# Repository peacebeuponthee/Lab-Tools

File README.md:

# Lab-Tools

1. Oscilloscope differential probe
2. Ultralow distortion sinewave generator

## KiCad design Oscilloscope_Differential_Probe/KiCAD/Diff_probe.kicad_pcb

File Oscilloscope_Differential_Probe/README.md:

Oscilloscope differential probe project based on reference design of Analog Devices.

The probe is based on the LTC6268-10 - 4GHz Ultra-Low Bias Current FET Input Op Amp from Analog Devices
https://www.analog.com/en/products/ltc6268-10.html#product-overview

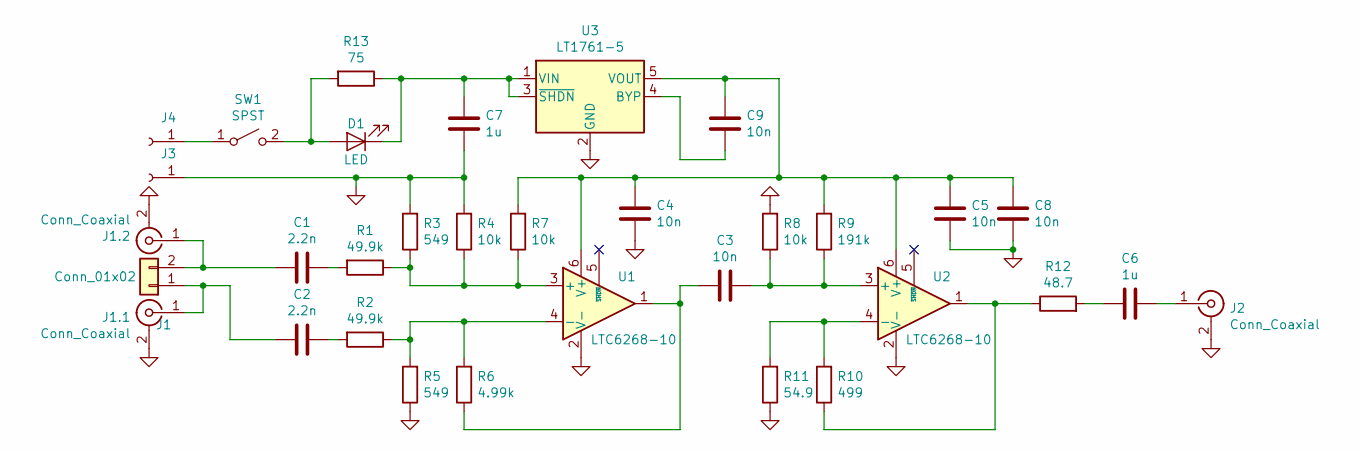
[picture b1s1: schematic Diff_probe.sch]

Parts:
C1, C2: 2.2n; C_1210_3225Metric; MouserID 80-C1210C222JDGAUTO
C3, C4, C5, C8, C9: 10n; C_0805_2012Metric; MouserID 80-C0805C103J5GECLR
C6, C7: 1u; C_0805_2012Metric; MouserID 80-C0805C105K4R
D1: LED; LED_1206_3216Metric; MouserID 604-APT3216LSECKJ4RV
J1: Conn_01x02; PinHeader_1x02_P2.54mm_Vertical; MouserID TSW-104-12-T-S-RA
J1.1, J1.2, J2: Conn_Coaxial; SMA_Samtec_SMA-J-P-X-ST-EM1_EdgeMount; MouserID 223-CON-SMA-EDGE-S
J3: Conn_01x01_Female; BatteryHolder_Keystone_593; MouserID 534-593
J4: Conn_01x01_Female; BatteryHolder_Keystone_594; MouserID 534-594
R1, R2: 49.9k; R_0805_2012Metric; MouserID 284-APC0805B49K9N
R3, R5: 549; R_0805_2012Metric; MouserID 667-ERA-6AEB5490V
R4, R7, R8: 10k; R_0805_2012Metric; MouserID 284-APC0805B10K0N
R6: 4.99k; R_0805_2012Metric; MouserID 284-APC0805B4K99N
R9: 191k; R_0805_2012Metric; MouserID 667-ERA-6AEB1913V
R10: 499; R_0805_2012Metric; MouserID 284-APC0805B499RN
R11: 54.9; R_0805_2012Metric; MouserID 667-ERA-6AEB54R9V
R12: 48.7; R_0805_2012Metric; MouserID 667-ERA-6AEB48R7V
R13: 75; R_1206_3216Metric; MouserID 71-CRCW120675R0FKEAC
SW1: SPST; SW_DIP_SPSTx01_Slide_6.7x4.1mm_W8.61mm_P2.54mm_LowProfile; MouserID 642-DM01
U1, U2: LTC6268-10; SOT-23-6; MouserID 584-C6268IS6-10TMPF
U3: LT1761-5; TSOT-23-5; MouserID 584-LT1761ES5-5TRPBF

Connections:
GND: C4.1, C5.1, C7.1, C8.1, J1.1.2 (Ext), J1.2.2 (Ext), J2.2 (Ext), J3.1, R3.2, R4.2, R5.1, R8.2, R11.1, U1.2 (V-), U2.2 (V-), U3.2 (GND)
unnamed: C1.1, R1.2
unnamed: C1.2, J1.2, J1.2.1 (In)
unnamed: C2.1, R2.2
unnamed: C2.2, J1.1, J1.1.1 (In)
unnamed: C3.1, R8.1, R9.1, U2.3 (+)
unnamed: C3.2, R6.1, U1.1
unnamed: C4.2, C5.2, C8.2, C9.2, R7.2, R9.2, U1.6 (V+), U2.6 (V+), U3.5 (VOUT)
unnamed: C6.1, R12.2
unnamed: C6.2, J2.1 (In)
unnamed: C7.2, D1.1 (K), R13.1, U3.1 (VIN), U3.3 (~SHDN)
unnamed: C9.1, U3.4 (BYP)
unnamed: D1.2 (A), R13.2, SW1.2 (B)
unnamed: J4.1, SW1.1 (A)
unnamed: R1.1, R3.1, R4.1, R7.1, U1.3 (+)
unnamed: R2.1, R5.2, R6.2, U1.4 (-)
unnamed: R10.1, R12.1, U2.1
unnamed: R10.2, R11.2, U2.4 (-)

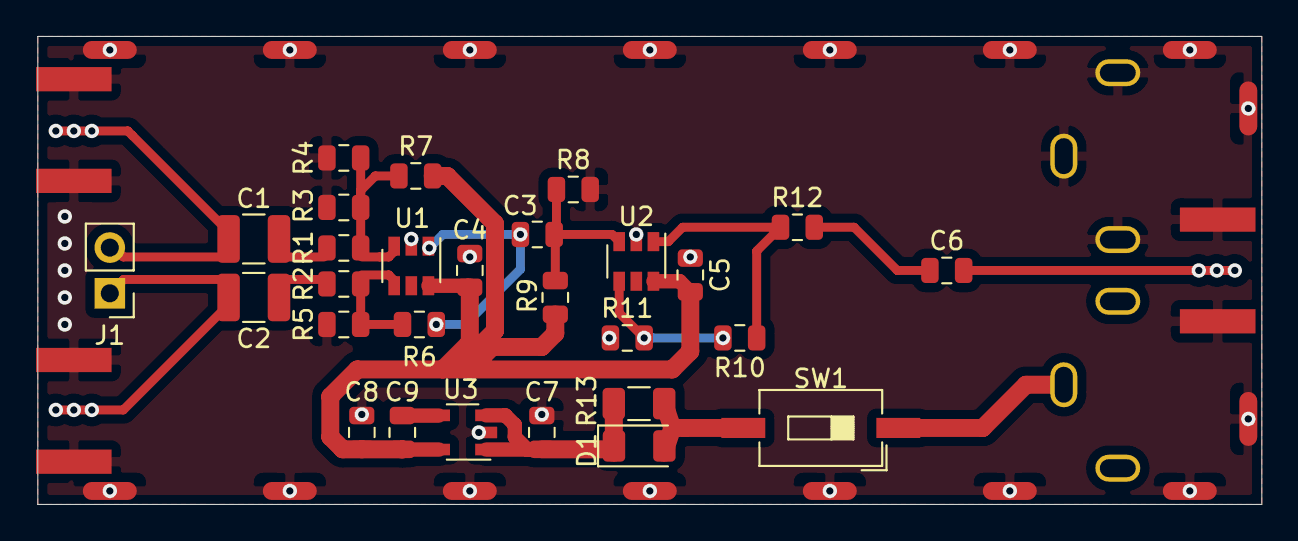
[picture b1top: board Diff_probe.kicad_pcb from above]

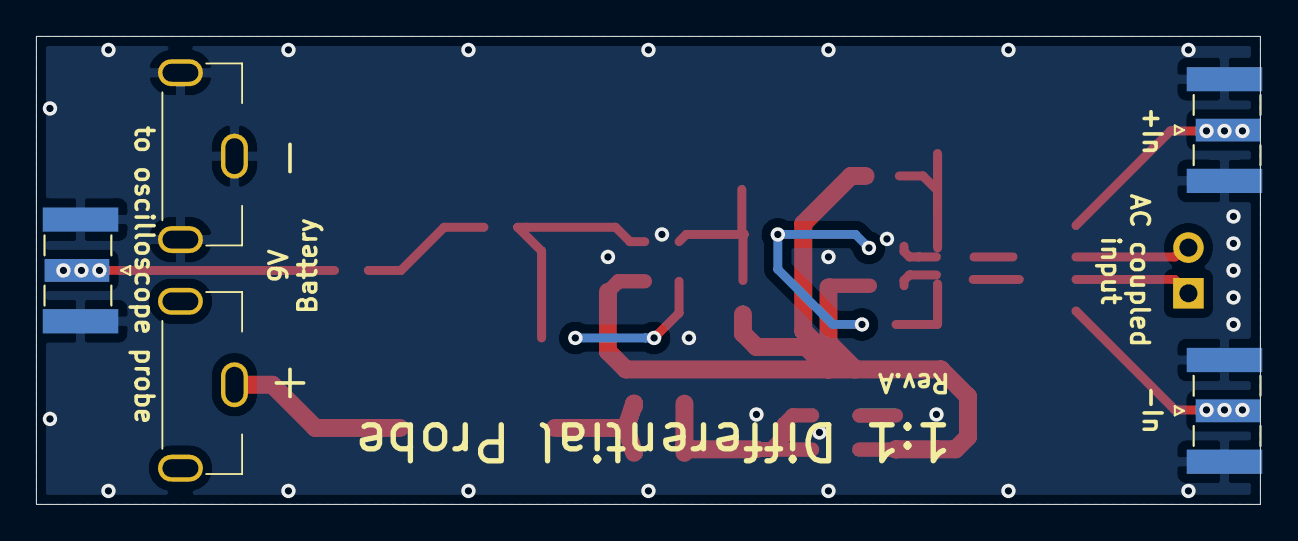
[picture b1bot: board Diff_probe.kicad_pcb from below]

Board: 2 copper layers, 68.0 x 26.0 mm, 33 parts (5 on the bottom side), 18 nets.

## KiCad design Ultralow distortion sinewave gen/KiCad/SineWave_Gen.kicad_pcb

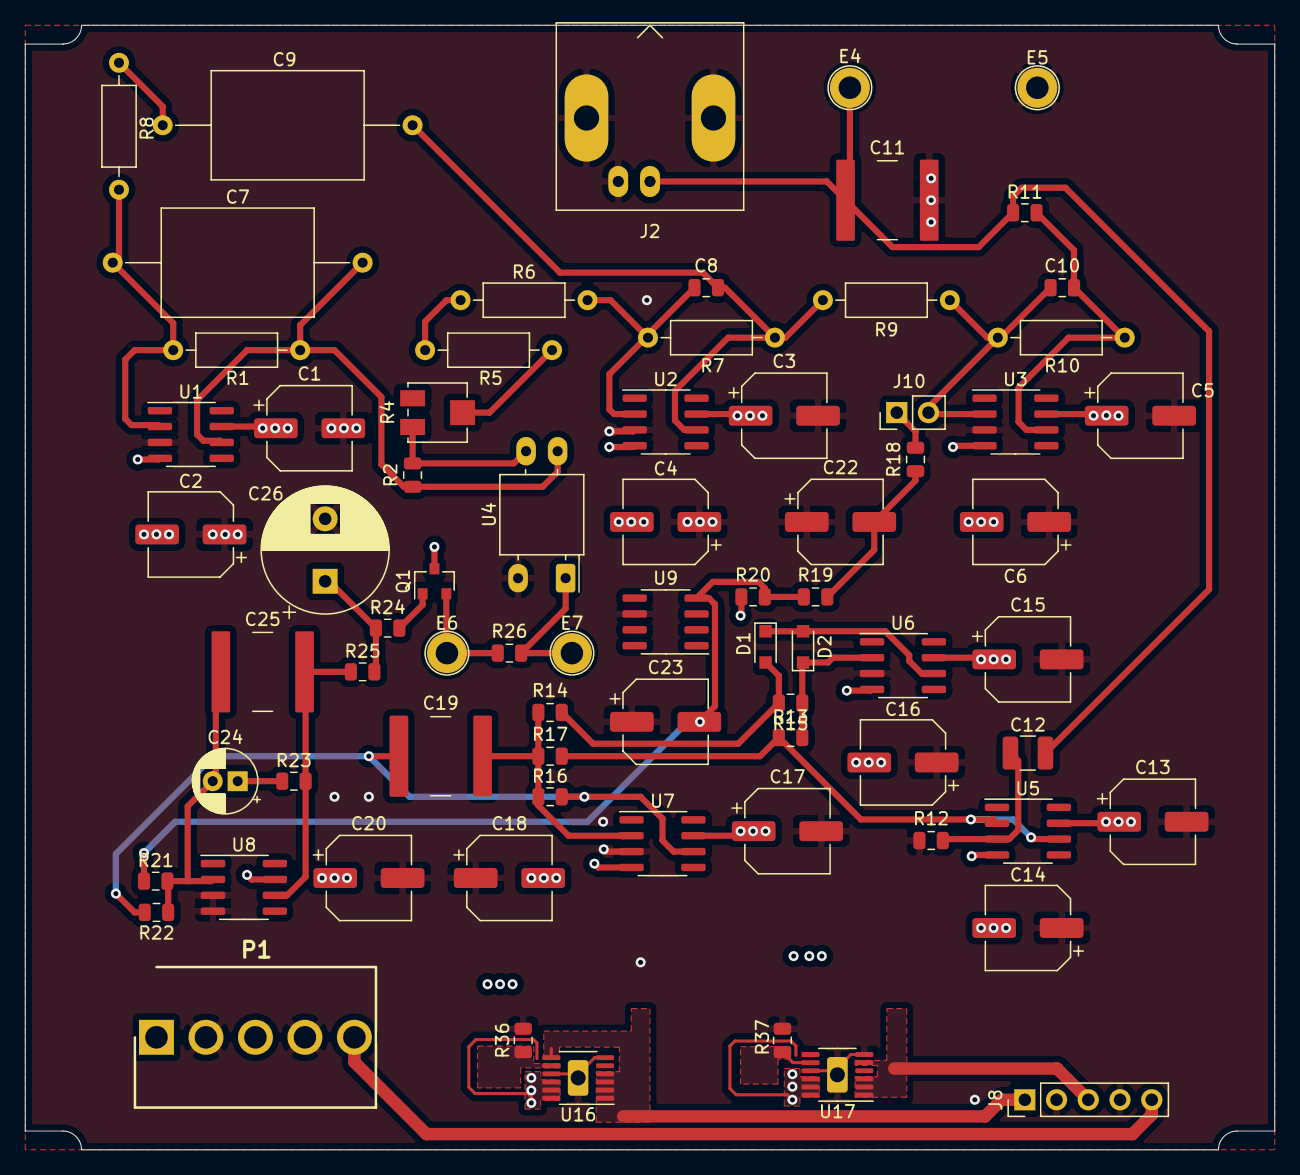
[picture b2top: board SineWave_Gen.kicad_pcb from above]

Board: 4 copper layers, 100.0 x 90.0 mm, 74 parts (0 on the bottom side), 36 nets.

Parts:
C1, C2, C3, C4, C5, C6, C13, C14, C15, C16, C17, C18, C20, C22, C23: 10u; CP_Elec_6.3x5.8
C7, C9: 0.01uF POLYSTYRENE; C_Axial_L12.0mm_D8.5mm_P20.00mm_Horizontal
C8: 5p MICA; C_0805_2012Metric
C10: 0.0068uF; C_0805_2012Metric
C11: 0.47u; C_2824_7260Metric_H5.0
C12: 0.1u; C_1210_3225Metric
C19, C25: 1u; C_2824_7260Metric_H5.0
C24: 22u; CP_Radial_D5.0mm_P2.00mm_L11mm
C26: 100u; CP_Radial_D10.0mm_P5.00mm_L16mm
D1, D2: 1N4148; D_SOD-323_HandSoldering
E4: SINE_OUT; TestPoint_THTPad_D3.2mm_Drill1.8mm
E5: GND; TestPoint_THTPad_D3.2mm_Drill1.8mm
E6: TP1; TestPoint_THTPad_D3.2mm_Drill1.8mm
E7: TP2; TestPoint_THTPad_D3.2mm_Drill1.8mm
J2: SINE_OUT; BNC_Molex_73138-5033_Horizontal
J8: Jumper; PinHeader_1x05_P2.54mm_Vertical
J10: Jumper; PinHeader_1x02_P2.54mm_Vertical
P1: Conn_01x05; Molex_Header_PCB_09-65-2058
Q1: MMBT3904; SOT-23
R1, R8: 7.87K 0.1%; R_Axial_DIN0207_L6.3mm_D2.5mm_P10.16mm_Horizontal
R2: 249; R_0805_2012Metric
R4: 500; Potentiometer_Bourns_3314J_Vertical
R5: 715 0.1%; R_Axial_DIN0207_L6.3mm_D2.5mm_P10.16mm_Horizontal
R6: 19.1K 0.1%; R_Axial_DIN0207_L6.3mm_D2.5mm_P10.16mm_Horizontal
R7: 40.2K 0.1%; R_Axial_DIN0207_L6.3mm_D2.5mm_P10.16mm_Horizontal
R9: 9.09K 0.1%; R_Axial_DIN0207_L6.3mm_D2.5mm_P10.16mm_Horizontal
R10: 12.1K 0.1%; R_Axial_DIN0207_L6.3mm_D2.5mm_P10.16mm_Horizontal
R11: 130; R_0805_2012Metric
R12: 1M; R_0805_2012Metric
R13, R15, R16, R17: 10K; R_0805_2012Metric
R14: 4.99K; R_0805_2012Metric
R18, R19: 12.1K; R_0805_2012Metric
R20: 4.3K; R_0805_2012Metric
R21: 100K; R_0805_2012Metric
R22: 28K; R_0805_2012Metric
R23: 36K; R_0805_2012Metric
R24: 100; R_0805_2012Metric
R25, R26: 470; R_0805_2012Metric
R36, R37: 120K; R_0805_2012Metric
U1, U2, U3: LT1468; SOIC-8_3.9x4.9mm_P1.27mm
U4: NSL-32; Luna_NSL-32
U5, U6, U7: LT1122; SOIC-8_3.9x4.9mm_P1.27mm
U8: LT1006; SOIC-8_3.9x4.9mm_P1.27mm
U9: LT1634-5; SOIC-8_3.9x4.9mm_P1.27mm
U16: LT3045xMSE; MSOP-12-1EP_3x4mm_P0.65mm_EP1.65x2.85mm
U17: LT3094xMSE; MSOP-12-1EP_3x4mm_P0.65mm_EP1.65x2.85mm

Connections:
/7: C11.1, C12.1, E4.1, J2.1, R11.1
/+V: C1.1, C3.1, C5.1, C13.1, C15.1, C17.1, C20.1, P1.3, Q1.3, U1.7, U2.7, U3.7, U5.7, U6.7, U7.7, U8.7, U16.10, U16.11, U16.12
/-V: C2.2, C4.2, C6.2, C14.2, C16.2, C18.2, P1.1, R20.2, U1.4, U2.4, U3.4, U5.4, U6.4, U7.4, U17.10, U17.11, U17.12
/PSU/+IN: J8.1, U16.1, U16.2, U16.3, U16.4, U16.7
/PSU/-IN: J8.3, U17.1, U17.2, U17.3, U17.5
GND: C1.2, C2.1, C3.2, C4.1, C5.2, C6.1, C11.2, C13.2, C14.1, C15.2, C16.1, C17.2, C18.1, C20.2, C22.1, C23.1, C26.2, E5.1, J2.2, J8.2, J8.4, P1.2, P1.4, R12.2, R36.2, R37.1, U1.3, U2.3, U3.3, U4.2, U6.3, U7.3, U8.3, U8.4, U9.6, U16.6, U16.9, U16.13, U17.6, U17.9, U17.13
unnamed: C7.1, R1.1, R2.2, U1.6, U4.4
unnamed: C7.2, R1.2, R8.2, U1.2
unnamed: C8.1, C9.1, R7.1, R9.2, U2.6
unnamed: C8.2, R6.1, R7.2, U2.2
unnamed: C9.2, R8.1
unnamed: C10.1, R10.1, R11.2, U3.6
unnamed: C10.2, J10.2, R9.1, R10.2, U3.2
unnamed: C12.2, R12.1, U5.3
unnamed: C19.1, R14.2, R16.1, R17.2, U7.2
unnamed: C19.2, R16.2, R22.2, U7.6
unnamed: C22.2, R18.2, R19.1
unnamed: C23.2, R19.2, R20.1, R21.1, U9.4
unnamed: C24.1, R23.1
unnamed: C24.2, C25.1, R21.2, R22.1, U8.2
unnamed: C25.2, R23.2, R25.1, U8.6
unnamed: C26.1, R24.1, R25.2
unnamed: R36.1, U16.8
unnamed: R37.2, U17.8
unnamed: D1.1, D2.2, U6.6
unnamed: D1.2, R14.1, R15.2
unnamed: D2.1, R13.2, R15.1, U6.2
unnamed: E6.1, Q1.2, R26.2
unnamed: E7.1, R26.1, U4.1
unnamed: J8.5, P1.5
unnamed: J10.1, R18.1
unnamed: Q1.1, R24.2
unnamed: R2.1, R4.3, U4.3
unnamed: R4.2, R5.2
unnamed: R5.1, R6.2
unnamed: R13.1, R17.1, U5.2, U5.6

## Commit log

2020-03-21 Differential probe
    Completed Rev.A
    PCB has been ordered on 21/03/2020
2020-03-21 Create Diffprobe_RevA_Gerber.zip
    Differential probe Rev.A gerber.
    Released for PCB manufacturing on 21/03/2020
2020-03-21 KiCAD project files
2020-03-21 BOM generated
2020-03-21 updated BOM
2020-03-21 BOM updated
2020-12-21 Upload sinewave gen
2020-12-21 Move kicad design to "KiCad" folder
